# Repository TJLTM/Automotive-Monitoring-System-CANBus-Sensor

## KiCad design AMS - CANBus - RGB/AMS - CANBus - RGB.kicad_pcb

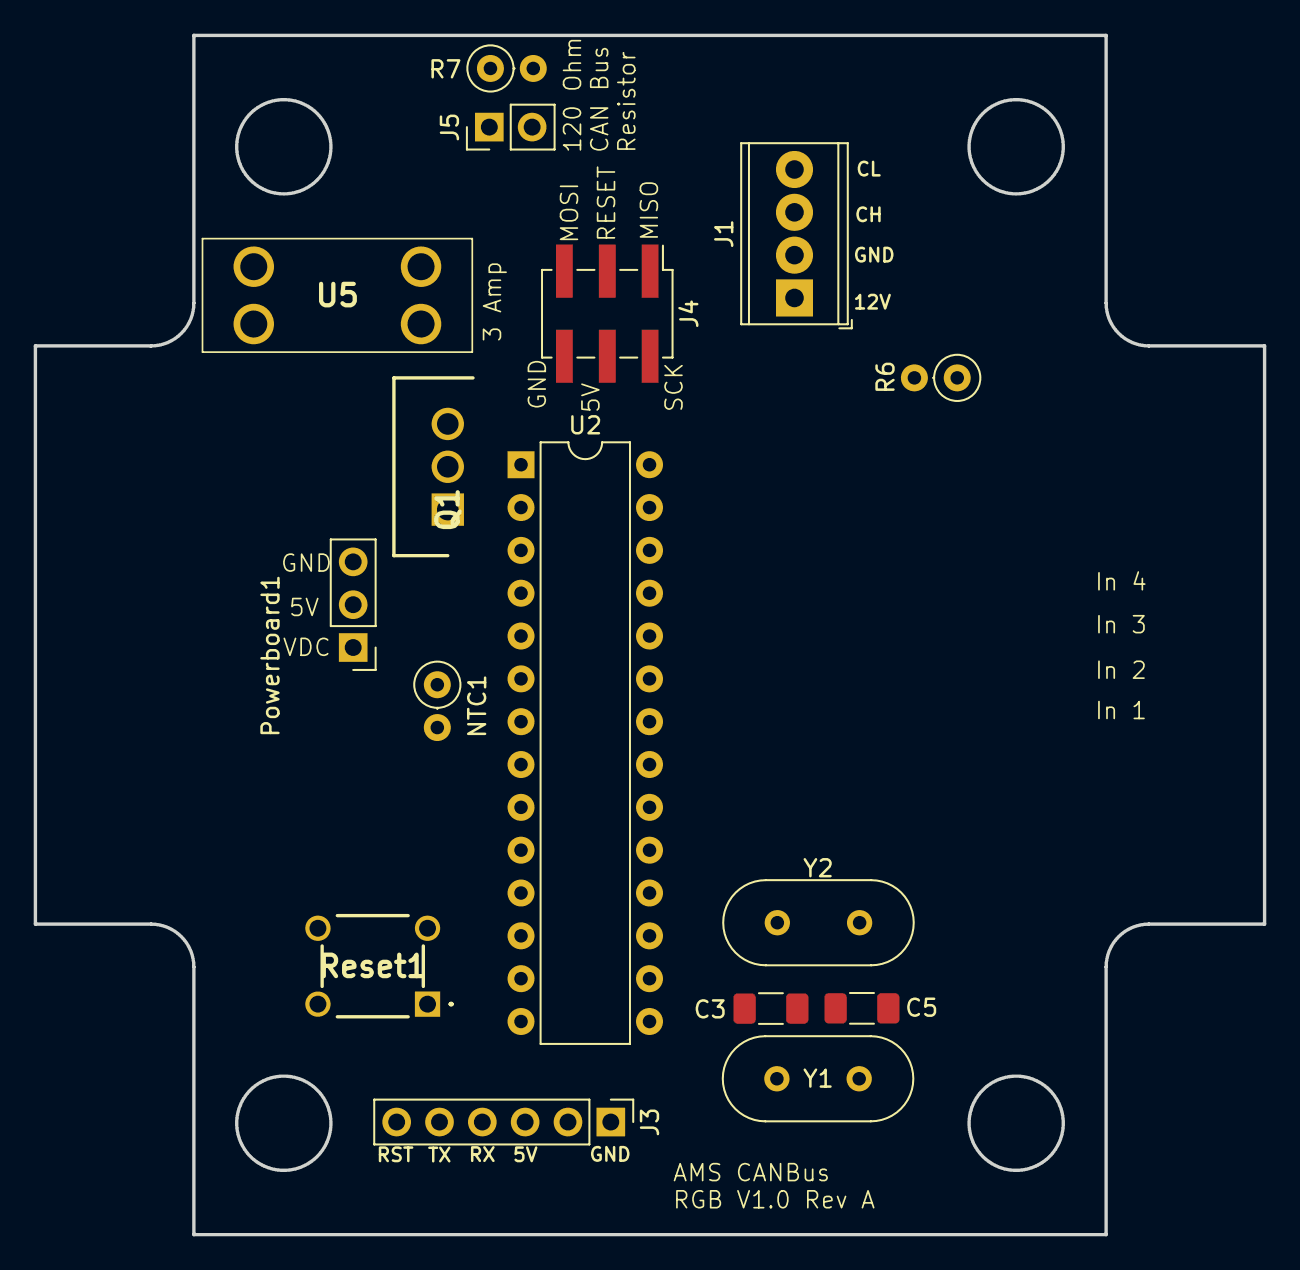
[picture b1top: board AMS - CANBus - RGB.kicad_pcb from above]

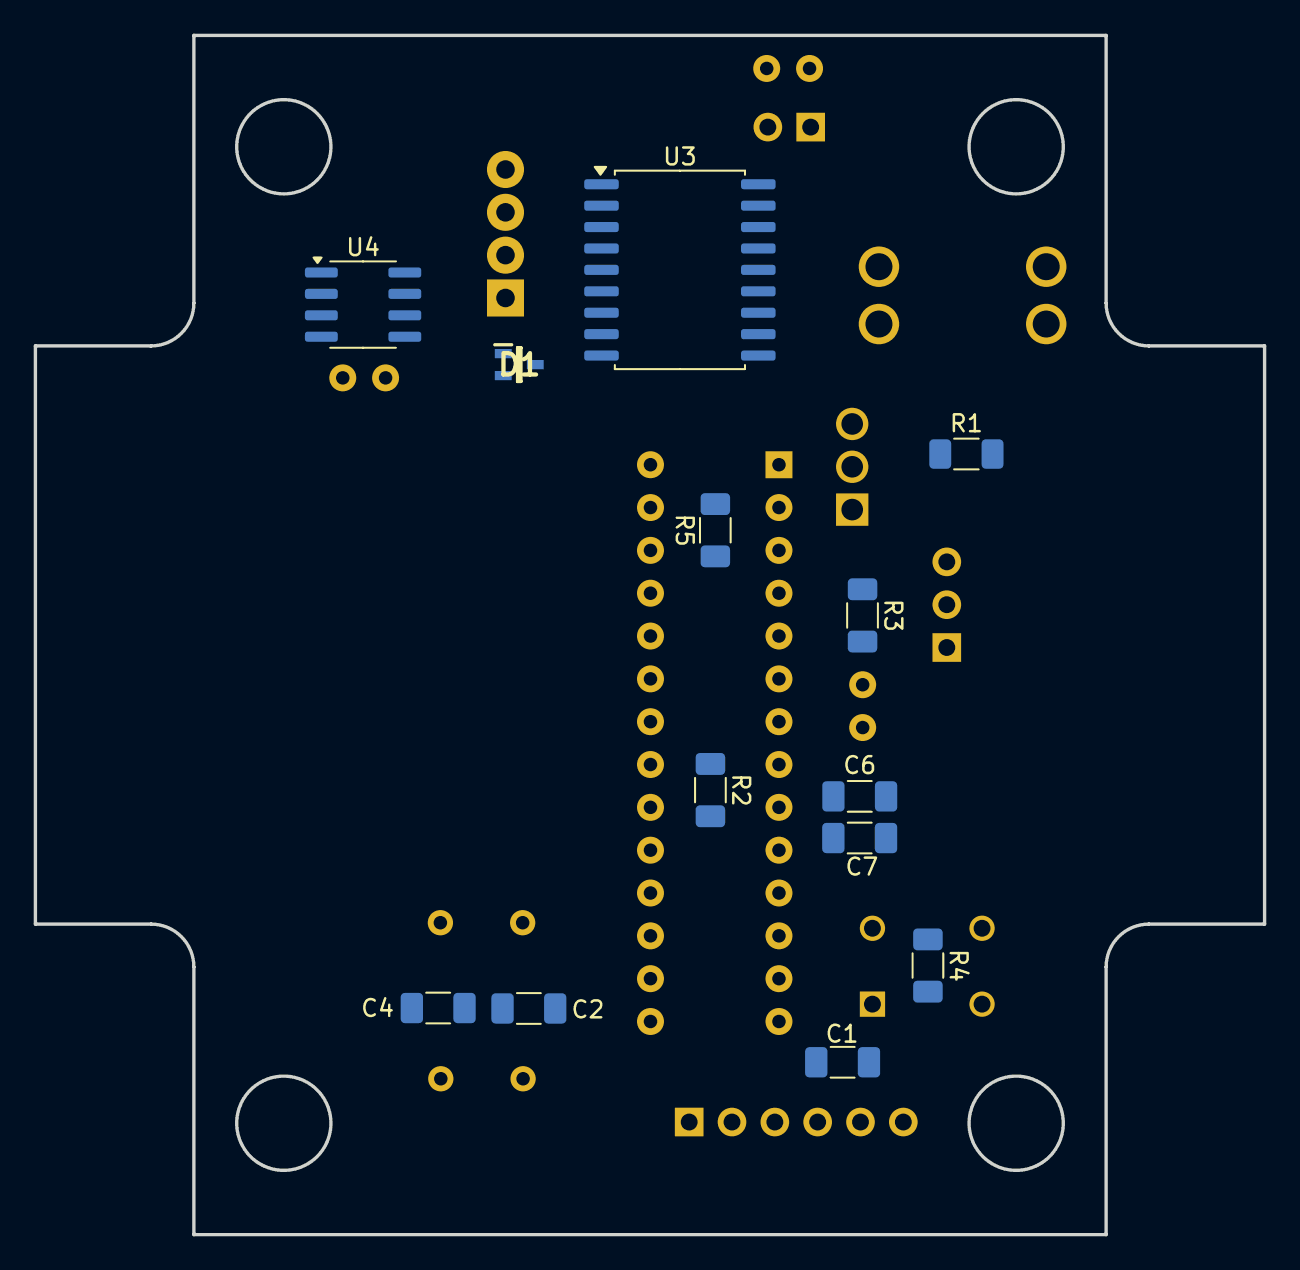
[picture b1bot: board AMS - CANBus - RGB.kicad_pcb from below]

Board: 2 copper layers, 72.9 x 71.1 mm, 29 parts (13 on the bottom side), 28 nets, no tracks yet.

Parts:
C1, C6, C7: 100nf; C_1206_3216Metric_Pad1.33x1.80mm_HandSolder
C2, C3, C4, C5: 22pf; C_1206_3216Metric_Pad1.33x1.80mm_HandSolder
D1: PESD5V0L2UU,115; SOT65P210X110-3N
J1: Power_And_CAN; TerminalBlock_Phoenix_MPT-0,5-4-2.54_1x04_P2.54mm_Horizontal
J3: TTL_Programmer; PinHeader_1x06_P2.54mm_Vertical
J4: ICSP; PinHeader_2x03_P2.54mm_Vertical_SMD
J5: Conn_01x02; PinHeader_1x02_P2.54mm_Vertical
NTC1: 10k; R_Axial_DIN0207_L6.3mm_D2.5mm_P2.54mm_Vertical
Powerboard1: Conn_01x03; PinHeader_1x03_P2.54mm_Vertical
Q1: IRF9Z34NPBF; TO254P469X1042X1967-3P
R1, R3, R4, R5: 10k; R_1206_3216Metric_Pad1.30x1.75mm_HandSolder
R2: 4.7k; R_1206_3216Metric_Pad1.30x1.75mm_HandSolder
R6: 17k; R_Axial_DIN0207_L6.3mm_D2.5mm_P2.54mm_Vertical
R7: 120; R_Axial_DIN0207_L6.3mm_D2.5mm_P2.54mm_Vertical
Reset1: TS02-66-160-BK-260-LCR-D; TS0266160BK260LCRD
U2: ATmega328P-P; DIP-28_W7.62mm
U3: MCP2515-xSO; SOIC-18W_7.5x11.6mm_P1.27mm
U4: MCP2551-I-SN; SOIC-8_3.9x4.9mm_P1.27mm
U5: 3568
Y1, Y2: 16MHz; Crystal_HC49-U_Vertical

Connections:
+5V: C6.1, C7.1, J3.3, J4.4, NTC1.2, Powerboard1.2, R2.2, R4.1, R5.2, U2.7 (VCC), U2.20 (AVCC), U3.18 (VDD), U4.3 (VDD)
+VDC: Powerboard1.1, U5.3, U5.4
/BareMinAtmel328P/AREF: R2.1, U2.21 (AREF)
/BareMinAtmel328P/PB1-D9: U2.15 (PB1), U3.16 (~CS)
/BareMinAtmel328P/PB3-D11-MOSI: J4.5, U2.17 (PB3), U3.14 (SI)
/BareMinAtmel328P/PB4-D12-MISO: J4.1, U2.18 (PB4), U3.15 (SO)
/BareMinAtmel328P/PB5-D13-SCK: J4.2, U2.19 (PB5), U3.13 (SCK)
/BareMinAtmel328P/PC0-A0: NTC1.1, R3.2, U2.23 (PC0)
/BareMinAtmel328P/PD0-RX: J3.4, U2.2 (PD0)
/BareMinAtmel328P/PD1-TX: J3.5, U2.3 (PD1)
/BareMinAtmel328P/PD2-D2: U2.4 (PD2), U3.12 (~INT)
/BareMinAtmel328P/RESET: C1.2, J4.3, R4.2, Reset1.1 (NO_1), U2.1 (~RESET/PC6)
/CANBUS-MCP2515/RXtoCANTC: U3.2 (RXCAN), U4.4 (RXD)
/CANBUS-MCP2515/TXtoCANTC: U3.1 (TXCAN), U4.1 (TXD)
CANBUS_H: D1.1 (CATHODE_1), J1.3, J5.1, U4.7 (CANH)
CANBUS_L: D1.2 (CATHODE_2), J1.4, R7.2, U4.6 (CANL)
GND: C2.2, C3.2, C4.2, C5.2, C6.2, C7.2, D1.3 (COMMON_ANODE), J1.2, J3.1, J4.6, Powerboard1.3, R1.2, R3.1, R6.2, Reset1.3 (COM_1), U2.8 (GND), U2.22 (GND), U3.9 (VSS), U4.2 (VSS)
unnamed: J1.1, Q1.2
unnamed: C1.1, J3.6
unnamed: J5.2, R7.1
unnamed: Q1.1, R1.1
unnamed: Q1.3, U5.1, U5.2
unnamed: C2.1, U2.9 (XTAL1/PB6), Y1.2
unnamed: C3.1, U2.10 (XTAL2/PB7), Y1.1
unnamed: C5.1, U3.8 (OSC1), Y2.1
unnamed: C4.1, U3.7 (OSC2), Y2.2
unnamed: R5.1, U3.17 (~RESET)
unnamed: R6.1, U4.8 (Rs)
